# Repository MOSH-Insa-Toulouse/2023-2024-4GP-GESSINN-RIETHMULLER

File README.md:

# Projet Capteur

## Description du projet

Ce projet a eu lieu dans le cadre de l'UF "du capteur au banc de test" en 4ème année de Génie physique à l'insa Toulouse. Le principe est d'établir une datasheet pour un capteur graphène soit une feuille de papier ou un tracé au crayon a papier est utilisé comme résistance.
Pour cela nous avons établis un banc de test avce differents composants arduino et avons utilisé le logiciel kikad pour créer un pcb pour les composants. Enfin nous avons éffectué des mesure pour déterminer la variation de la résistance en fonction du graphène et de la flexion du papier.
Nous avons utilisé un écran OLED sur le pcb pour choisir entre la mesure du capteur grapehène et d'un flex sensor et avons crée une application android pour avoir les valeurs de mesures sur le téléphone à l'aide d'une communication bluetooth.

Le Capteur ressemble à ça : 

## Livrables

* PCB shield pour arduino uno
* Code arduino
* Banc de test du capteur
* Application android qui fonctionne par bluetooth
* Datasheet

## Materiel Utilisé

* Ecran OLED
* Flex sensor
* Encodeur Rotatoire
* Capteur Graphène
* Module Bluetooth
* LCT-1050
* MCP 41050
* Résistances : 2x100kOhm, 1x33kOhm, 1*10kOhm, 1x1kOhm
* Capacités : 2x100nF, 1x1uF

## PCB Shield Pour Arduino Uno
### Partie Kikad

Nous avons commencé par mettre en place un shematic pour notre PCB. Pour cela, nous avons tout d'abord utilisé un template pour arduino uno et nous avons ensuite crée les empreintes et shematic pour chacun des composants sur notre plaque. Ensuite nous avons relié les entrées de chacun des composants aux entrées de l'arduino. Pour cela nous avons du faire des choix que l'on peut retrouver dans le document ci dessous :

https://github.com/MOSH-Insa-Toulouse/2023-2024-4GP-RIETHMULLER-GESSINN/blob/main/Projet%20Capteur%20composants.docx

Nous anvons ensuite procédé à l'organisation de la partie PCB. Nous avons disposé tout les elements sur la plaque et avons relié de façon à avoir un plan de masse sur la plaque et éviter d'avoir a faire des vias. Nous avons choisi d'avoir les pistes sur le dessus du PCB et d'avoir que des composants traverstants. Vous pouvez voir ci dessous le PCB à l'état fini.

### Impression du PCB 

Lorsque nous avions fini le PCB il fallait le réaliser. Avec l'aide de Catherine Crouzet nous avons imprimé notre plan de PCB et l'avons réalisé dans l'atelier du Batiment Génie Electrique. Nous avons ensuite percé la plaque à l'aide de forets de 1 ou 0.8 mm. Nous avons ensuite soudé les composant et ajouté des supports pour pouvoir déposer le PCB directement sur l'arduino UNO. Nous avons ensuite effectué des test de contact électrique de nos composants pour vérifier que tout était comme prévu et avons remarqué qu'il y avait une erreur.

Au niveau du premier point, deux pistes ne devant pas être relièes entraient en contact et au niveau du seconc, le plan de masse que devait être supposement relié à la masse ne l'était pas. Nous avons donc du remedier à ces problèmes avant de passer à la suite, pour cela nous avons bricolé pour éviter de devoir imprimer le PCB une seconde fois. Nous avons également corrigé cela sur le ficher Kikad qui se trouve sur le dossier en décalent simplement une réistance pour laisser l'espace nécessaire au plan de masse et au passage paralèlle des deux pistes.

## Code Arduino
Le code Arduino permet d'effectuer l'acquisition des mesures sur le capteur graphène et sur le flex sensor. Ces mesures sont a la fois affichées sur l'écran Oled et transmies au capteur bluetooth qui pourra les transmettre a un téléphone portable grace à l'application. Vous pouvez retrouver le code dans le dossier "Code Capteur Resistif ". Le code est annoté pour étre le plus lisible possible et suis les pins utilisés dans la partie KIKAD.
## Banc de test
Pour les tests nous avons utilisé le banc de tets à disposition et avons éffectué le mesures de la facon suivante :

Il y 7 étages qui entrainent une déformation différente a chaque fois. Pour le capteur graphène nous avons mesuré pour chaque échelon la variation de resistance en tension et en déformation. Nous avons également réalisé des mesures sur le flex sensor afin de pouvoir comparer. Pour le flex sensor nous avons uniquement procédé en compression car celui-ci n'est fiable que dans un sens.

Les résusltats de nos mesures sont à retrouver dans la partie Datasheet.

## Application android

Pour la conception de notre application, nous avons utilisé le site MIP App Inventor, le but étant d'avoir accès au résultats de nos mesures sur un téléphone par communication Bluetooth. Pour cela nous avons utilisé un "Listpicker" pour connecter l'appareil au téléphone.
Nous avons ensuite utilisé le module bluetooth pour récuperer 2 messages de 1 octet chacun. Nous avons utilisé un clock pour calibrer l'intervale entre les mesures recues afin d'avoir le même que dans le code. Pour finir nous avons effectué du traitement de données afin d'avoir la variation de la résistance ainsi que les deux valeurs de resistance. Le code donne ceci:

Comme on peut le voir dans les blocks nous avons utilisé plusieurs variables globales notamment pour les calculs de la résistance du flex sensor. Nous avons également multiplié toutes les mesures recues par 4 car nous les avions divisées par 4 dans le code arduino pour que chaque mesure passe dans un octet. 

Pour ce qui est de la face avant, nous avons choisis un interface relativement simple: 

Nous avons un bouton de connexion Bluetooth qui permet de choisir l'appareil à connecter. Nous avons ensuite ajouté des boutons d'arrêt de clock pour pouvoir stopper l'arrivée des mesures si souhaité. Le reste de l'interface est uniquement de l'affichage des mesures.

## Datasheet
Nos avons réalisé de mesures en utilisant differentes valeurs de déformation et nous avons utilisé des crayons à mine H, HB et 2B.
Nous avons également réalisé de mesures sur le flex sensor en compression.
On peut voir d'abord les mesures en compression :

Et ensuite les mesures en tension : 

## Contacts

Pour toute remarque ou information complémentaire, n'hésitez pas à nous contacter :
* Clément GESSINN : cgessinn@insa-toulouse.fr
* Théo RIETHMULLER : riethmul@insa-toulouse.fr

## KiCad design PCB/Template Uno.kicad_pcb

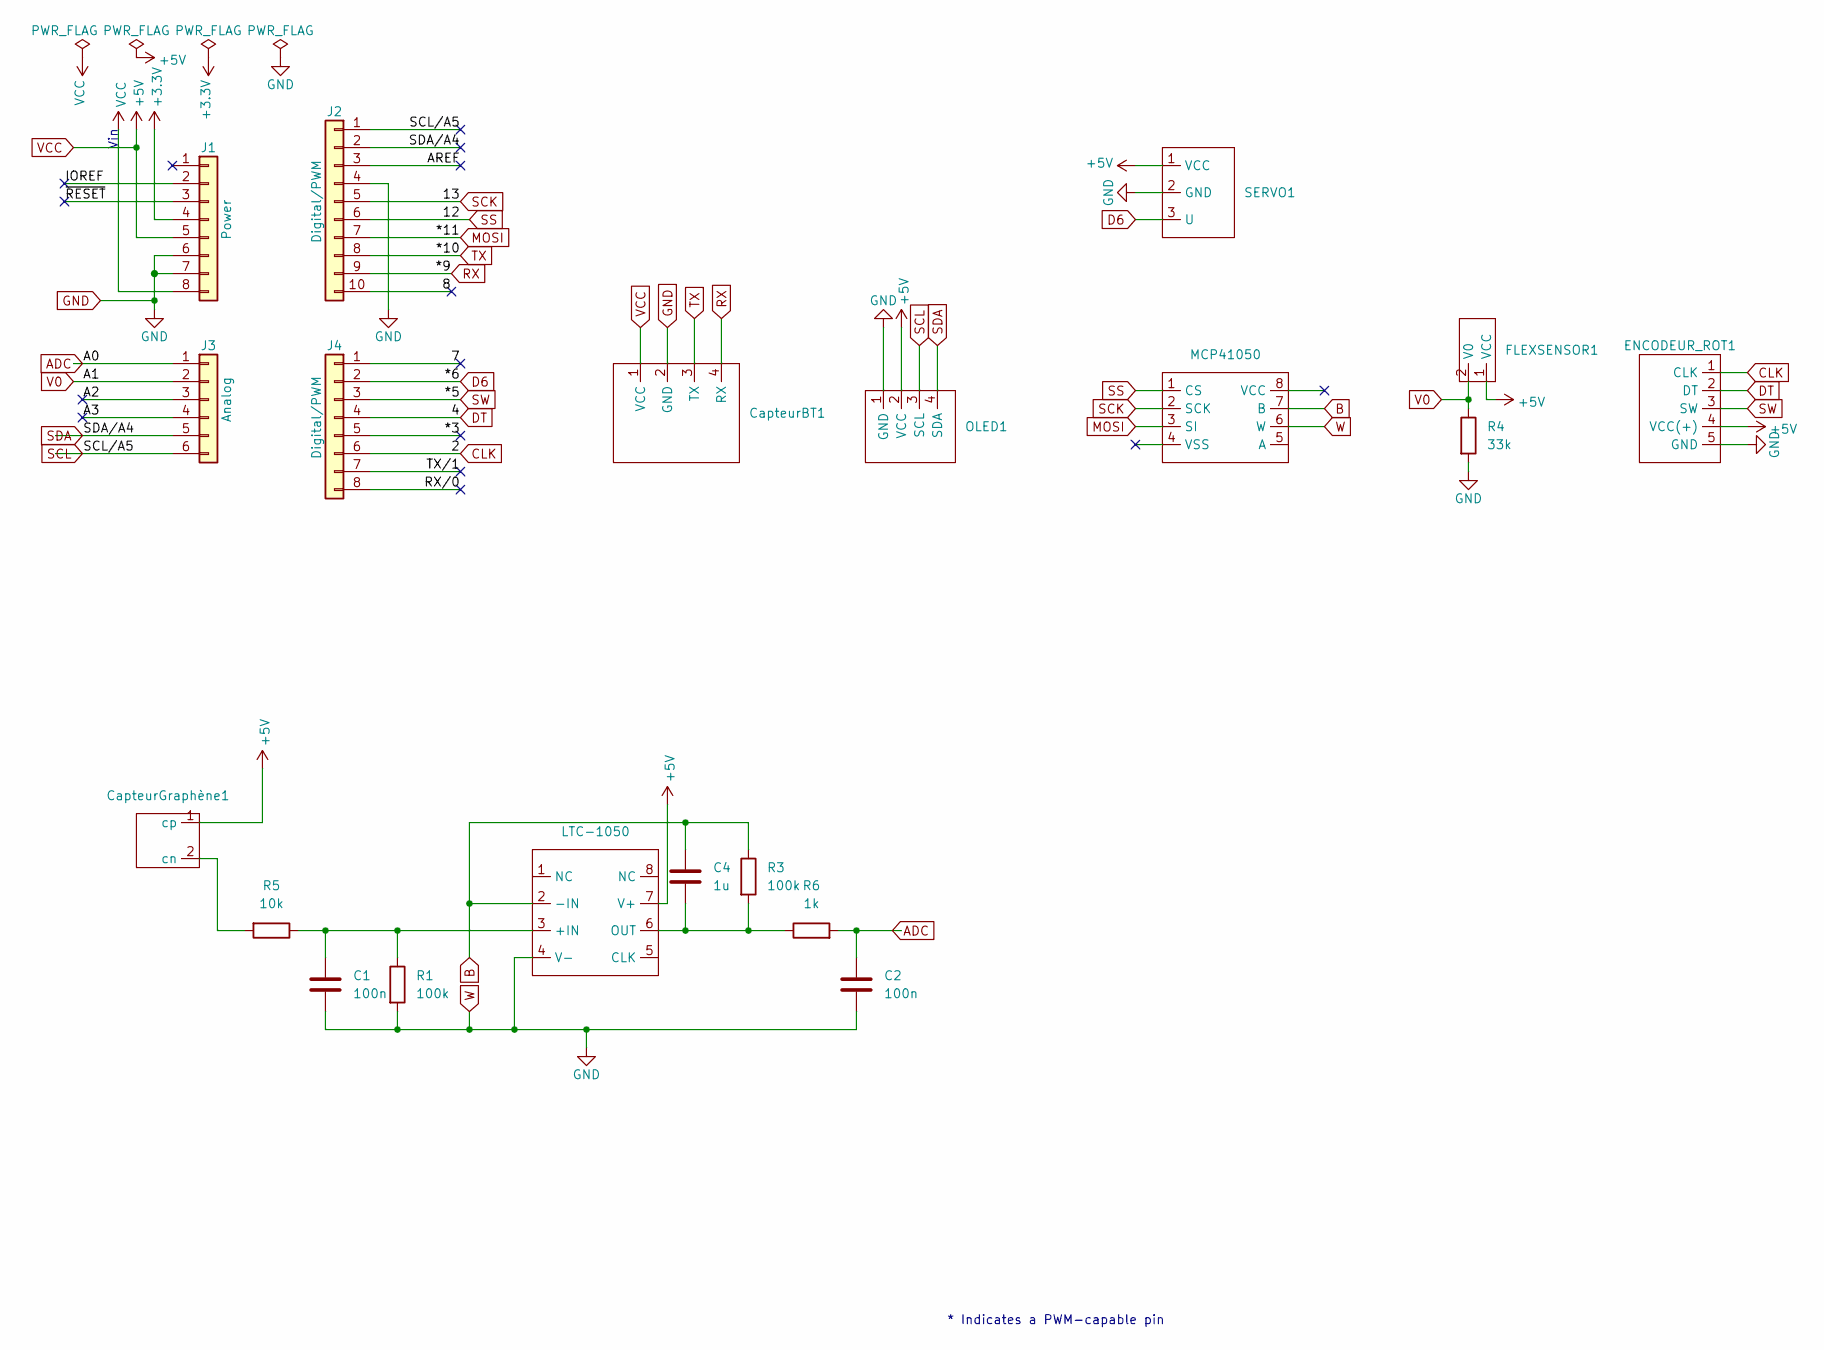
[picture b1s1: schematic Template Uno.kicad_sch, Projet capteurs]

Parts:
C1, C2: 100n; C_Disc_D5.1mm_W3.2mm_P5.00mm
C4: 1u; C_Rect_L7.0mm_W3.5mm_P5.00mm
CapteurBT1: BT
CapteurGraphène1: CAPTEUR GRAPHENE
ENCODEUR_ROT1: ENCODEUR KY-040
FLEXSENSOR1: FLEX SENSOR
J1: Power; PinSocket_1x08_P2.54mm_Vertical
J2: Digital/PWM; PinSocket_1x10_P2.54mm_Vertical
J3: Analog; PinSocket_1x06_P2.54mm_Vertical
J4: Digital/PWM; PinSocket_1x08_P2.54mm_Vertical
LTC-1050: LTC-1050
MCP41050: POTENTIOMETRE DIGITAL
OLED1: OLED
R1, R3: 100k; R_Axial_DIN0207_L6.3mm_D2.5mm_P10.16mm_Horizontal
R4: 33k; R_Axial_DIN0207_L6.3mm_D2.5mm_P10.16mm_Horizontal
R5: 10k; R_Axial_DIN0207_L6.3mm_D2.5mm_P10.16mm_Horizontal
R6: 1k; R_Axial_DIN0207_L6.3mm_D2.5mm_P10.16mm_Horizontal
SERVO1: SERVO

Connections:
+3V3: J1.4
/7: J4.1
/8: J2.10
/*3: J4.5
/A2: J3.3
/A3: J3.4
/AREF: J2.3
/IOREF: J1.2
/RX/0: J4.8
/TX/1: J4.7
/~RESET: J1.3
ADC: C2.1, J3.1, R6.2
B: C4.1, LTC-1050.2 (-IN), MCP41050.7 (B), R3.1
CLK: ENCODEUR_ROT1.1 (CLK), J4.6
D6: J4.2, SERVO1.3 (U)
DT: ENCODEUR_ROT1.2 (DT), J4.4
GND: C1.2, C2.2, CapteurBT1.2 (GND), ENCODEUR_ROT1.5 (GND), J1.6, J1.7, J2.4, LTC-1050.4 (V-), MCP41050.6 (W), OLED1.1 (GND), R1.2, R4.2, SERVO1.2 (GND)
MOSI: J2.7, MCP41050.3 (SI)
unnamed: CapteurGraphène1.2 (cn), R5.2
unnamed: C1.1, LTC-1050.3 (+IN), R1.1, R5.1
unnamed: C4.2, LTC-1050.6 (OUT), R3.2, R6.1
RX: CapteurBT1.4 (RX), J2.9
SCK: J2.5, MCP41050.2 (SCK)
SCL: J2.1, J3.6, OLED1.3 (SCL)
SDA: J2.2, J3.5, OLED1.4 (SDA)
SS: J2.6, MCP41050.1 (CS)
SW: ENCODEUR_ROT1.3 (SW), J4.3
TX: CapteurBT1.3 (TX), J2.8
V0: FLEXSENSOR1.2 (V0), J3.2, R4.1
VCC: CapteurBT1.1 (VCC), CapteurGraphène1.1 (cp), ENCODEUR_ROT1.4 (VCC(+)), FLEXSENSOR1.1 (VCC), J1.5, J1.8, LTC-1050.7 (V+), OLED1.2 (VCC), SERVO1.1 (VCC)

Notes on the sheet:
Vin
* Indicates a PWM-capable pin

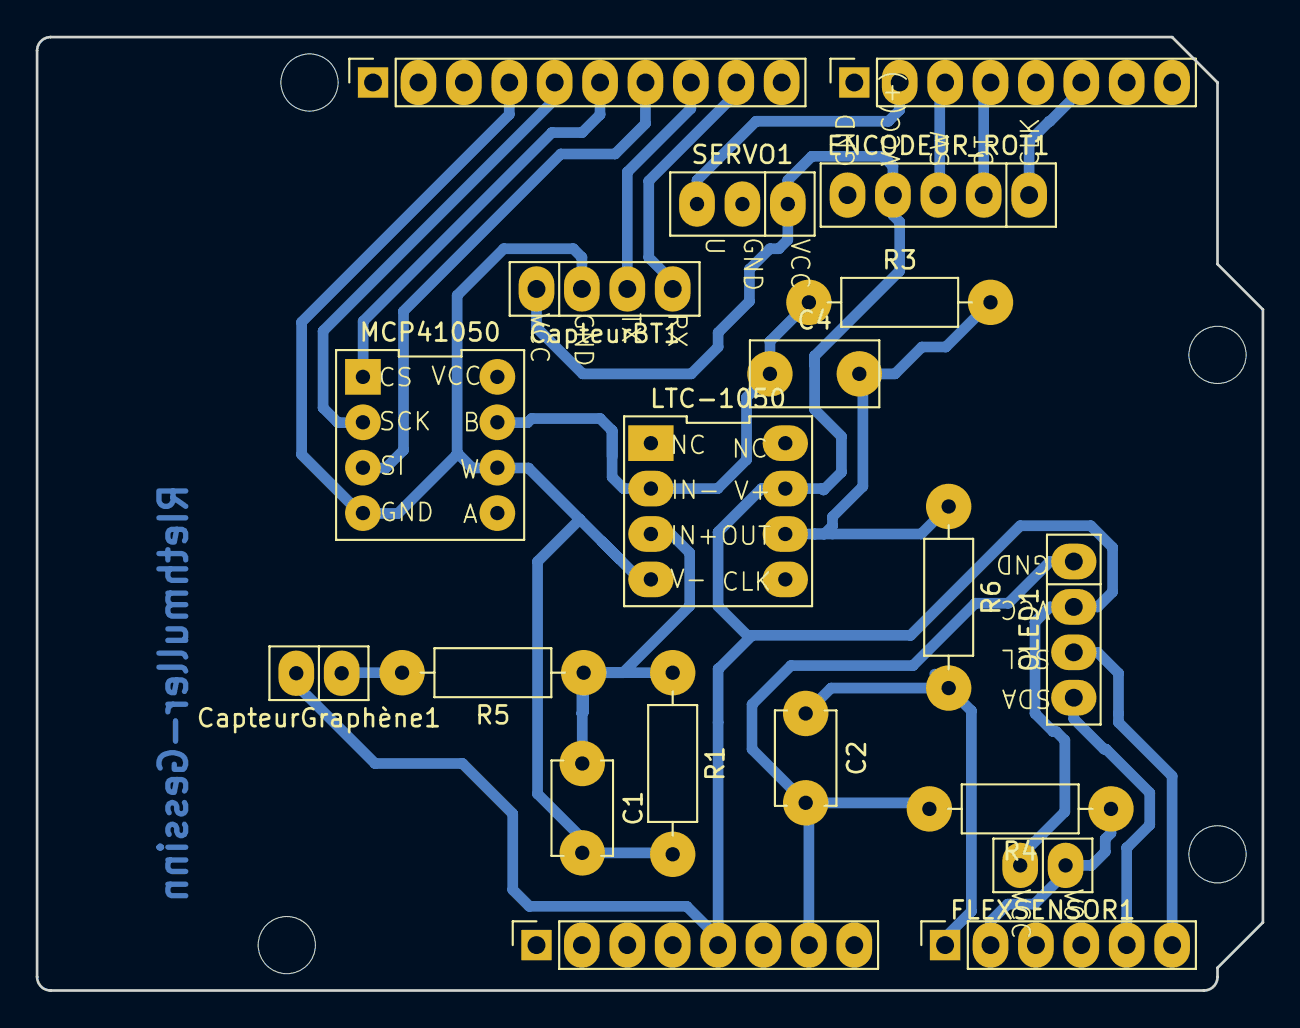
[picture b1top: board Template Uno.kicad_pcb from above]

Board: 2 copper layers, 68.6 x 53.3 mm, 24 parts (0 on the bottom side), 19 nets.

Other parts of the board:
MH1, MH2, MH3, MH4: MountingHole_3.2mm

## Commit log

2024-05-21 Datasheet_a_ajouter
2024-05-29 Fin README.md
